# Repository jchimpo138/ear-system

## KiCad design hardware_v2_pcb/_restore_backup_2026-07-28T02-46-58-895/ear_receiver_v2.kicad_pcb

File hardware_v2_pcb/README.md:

# v2.0 Custom All-in-One Ear PCB Architecture (KiCad 10)

> **Overview:** Universal 25mm–30mm Circular All-in-One Custom PCB for Disney Interactive Ear Receiver Wearables.

---

## 1. Silicon Chipset Specifications

| Component Subsystem | Chipset / Part Number | Manufacturer | Key Specification / Function |
|---|---|---|---|
| **Microcontroller & BLE** | **nRF52840-QIAA** (or **nRF52840-MINI** module) | Nordic Semiconductor | 32-bit ARM Cortex-M4F, 4.8mA active BLE RX, 1.5µA System OFF sleep |
| **LiPo Battery Charger** | **MCP73831T-2ACI/OT** | Microchip | SOT-23-5 Linear Charger, $R_{\text{PROG}} = 2.0\text{k}\Omega$ (**Strict 500mA 1C MAX Limit**) |
| **5V LED Boost Converter** | **TPS61023DRLR** | Texas Instruments | Synchronous Step-Up Boost ($3.0\text{V}-4.2\text{V} \rightarrow 5.0\text{V} @ 3.0\text{A}$), 95% efficiency, `EN` pin control |
| **Battery Fuel Gauge** | **MAX17048G+T10** | Analog Devices / Maxim | I2C ModelGauge battery percentage % & voltage sensor |
| **Real-time Current Monitor** | **INA219AIDR** | Texas Instruments | I2C High-side current & power meter |
| **3-Axis Motion Sensor** | **LIS3DSH** (or **BMI270**) | STMicroelectronics / Bosch | I2C Accelerometer with `INT1` hardware wake interrupt pin |
| **Vibration Motor Driver** | **SI2302CDS-T1-GE3** | Vishay / Diodes Inc | N-Channel MOSFET ($V_{DS}=20\text{V}, I_D=2.8\text{A}$), SOT-23 package |
| **USB Charging Port** | **TYPE-C-31-M-12** (16-pin USB-C) | Midya / C&K | USB 2.0 16-pin USB-C connector with dual $5.1\text{k}\Omega$ CC pull-down resistors |

---

## 2. Pin Netlist Mapping (nRF52840)

| nRF52840 GPIO Pin | Connected Signal Net | Function |
|---|---|---|
| **P0.06** | `I2C_SDA` | Shared I2C Data Line (LIS3DSH, MAX17048, INA219) |
| **P0.08** | `I2C_SCL` | Shared I2C Clock Line (LIS3DSH, MAX17048, INA219) |
| **P0.10** | `MOTION_INT1` | Hardware Wake-On-Motion Interrupt from LIS3DSH |
| **P0.12** | `NEOPIXEL_DATA` | FastLED / WS2812B 2020 Data Signal Output |
| **P0.15** | `HAPTIC_PWM` | PWM Control Signal to SI2302 MOSFET Gate |
| **P0.17** | `BOOST_ENABLE` | High = Enable 5V Boost Converter, Low = Shut Down 5V Boost |
| **P0.20** | `KEY_BUTTON` | Input with Pull-Up for External Tactile Power Switch |

---

## 3. PCB Layout Guidelines
- **Board Shape:** Circular PCB, $\varnothing 25.0\text{mm} - 30.0\text{mm}$.
- **USB-C Placement:** Edge-mounted on the bottom perimeter.
- **Layer Count:** 2-Layer (or 4-Layer with internal GND / Power planes for optimal RF performance).
- **Antenna:** On-board Meander Inverted-F PCB Trace Antenna or 2.4GHz Chip Antenna.

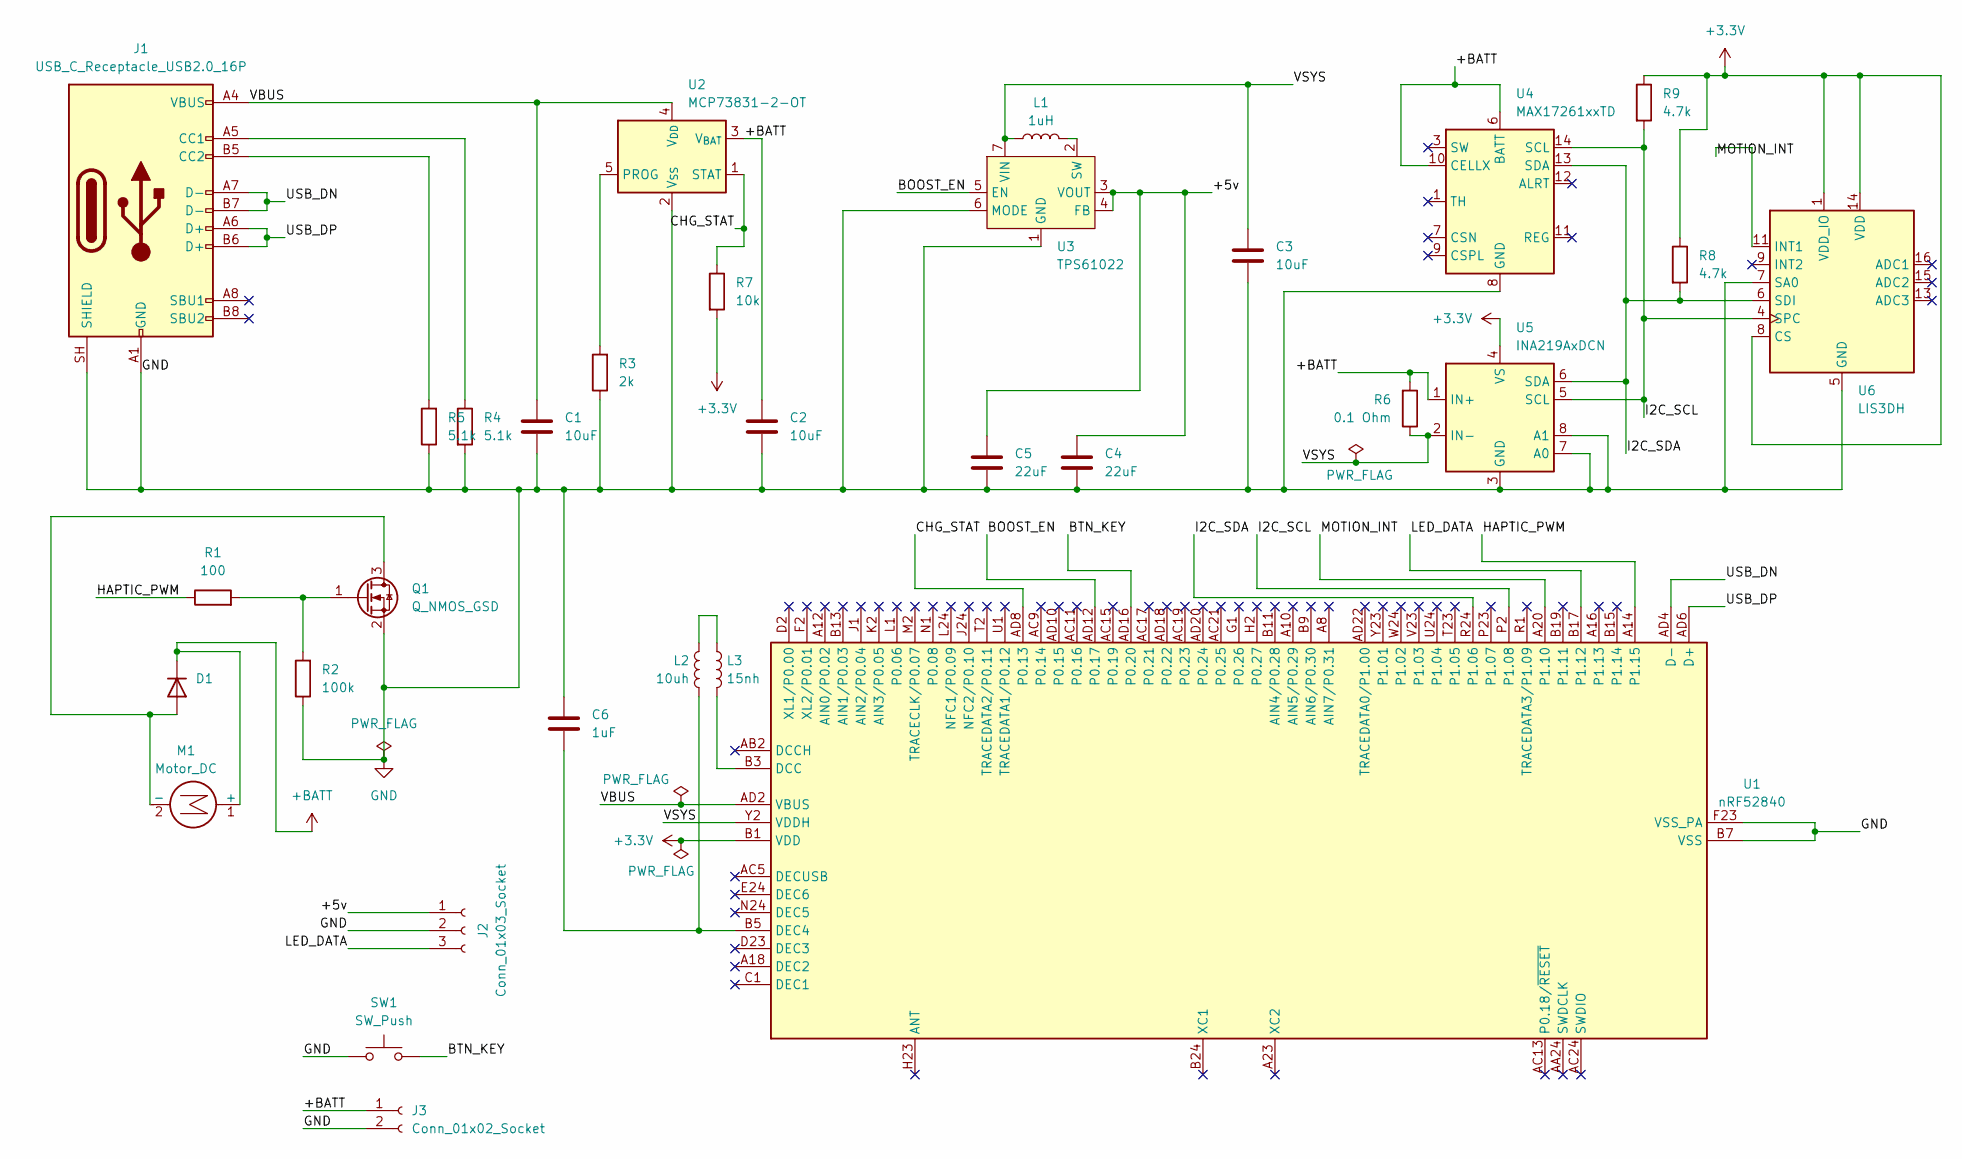
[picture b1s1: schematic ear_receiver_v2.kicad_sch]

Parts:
C1, C2, C3: 10uF; C_0603_1608Metric
C4, C5: 22uF; C_0603_1608Metric
C6: 1uF; C_0603_1608Metric
D1: 1N4148W; D_SOD-123
J1: USB_C_Receptacle_USB2.0_16P; USB_C_Receptacle_GCT_USB4105-xx-A_16P_TopMnt_Horizontal
J2: Conn_01x03_Socket; JST_PH_S3B-PH-K_1x03_P2.00mm_Horizontal
J3: Conn_01x02_Socket; JST_PH_S2B-PH-K_1x02_P2.00mm_Horizontal
L1: 1uH; L_0603_1608Metric
L2: 10uh; L_0402_1005Metric
L3: 15nh; L_0402_1005Metric
M1: Motor_DC; PinHeader_1x02_P2.54mm_Vertical
Q1: Q_NMOS_GSD; SOT-23
R1: 100; R_0603_1608Metric
R2: 100k; R_0603_1608Metric
R3: 2k; R_0603_1608Metric
R4, R5: 5.1k; R_0603_1608Metric
R6: 0.1 Ohm; R_1206_3216Metric
R7: 10k; R_0603_1608Metric
R8, R9: 4.7k; R_0603_1608Metric
SW1: SW_Push; SW_SPST_B3U-3000P-B
U1: nRF52840; Nordic_AQFN-73-1EP_7x7mm_P0.5mm
U2: MCP73831-2-OT; SOT-23-5
U3: TPS61022; Texas_RWU0007A_VQFN-7_2x2mm_P0.5mm
U4: MAX17261xxTD; TDFN-14-1EP_3x3mm_P0.4mm_EP1.78x2.35mm
U5: INA219AxDCN; SOT-23-8
U6: LIS3DH; LGA-16_3x3mm_P0.5mm_LayoutBorder3x5y

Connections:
+3.3V: R7.2, R8.1, R9.1, U1.A22 (VDD), U1.AD14 (VDD), U1.AD23 (VDD), U1.B1 (VDD), U1.W1 (VDD), U5.4 (VS), U6.1 (VDD_IO), U6.8 (CS), U6.14 (VDD)
+BATT: C2.2, D1.1 (K), J3.1, M1.1 (+), R6.2, U2.3 (V_{BAT}), U4.6 (BATT), U4.10 (CELLX), U5.1 (IN+)
/+5v: C4.1, C5.1, J2.1, U3.3 (VOUT), U3.4 (FB)
/BOOST_EN: U1.AD12 (P0.17), U3.5 (EN)
/BTN_KEY: SW1.2, U1.AD16 (P0.20)
/CHG_STAT: R7.1, U1.AD8 (P0.13), U2.1 (STAT)
/HAPTIC_PWM: R1.1, U1.A14 (P1.15)
/I2C_SCL: R9.2, U1.P2 (P1.08), U4.14 (SCL), U5.5 (SCL), U6.4 (SPC)
/I2C_SDA: R8.2, U1.R24 (P1.06), U4.13 (SDA), U5.6 (SDA), U6.6 (SDI)
/LED_DATA: J2.3, U1.B17 (P1.12)
/MOTION_INT: U1.A20 (P1.10), U6.11 (INT1)
/USB_DN: J1.A7 (D-), J1.B7 (D-), U1.AD4 (D-)
/USB_DP: J1.A6 (D+), J1.B6 (D+), U1.AD6 (D+)
/VBUS: C1.2, J1.A4 (VBUS), J1.A9 (VBUS), J1.B4 (VBUS), J1.B9 (VBUS), U1.AD2 (VBUS), U2.4 (V_{DD})
/VSYS: C3.1, L1.1, R6.1, U1.Y2 (VDDH), U3.7 (VIN), U5.2 (IN-)
GND: C1.1, C2.1, C3.2, C4.2, C5.2, C6.1, J1.A1 (GND), J1.A12 (GND), J1.B1 (GND), J1.B12 (GND), J1.SH (SHIELD), J2.2, J3.2, Q1.2 (S), R2.1, R3.1, R4.2, R5.1, SW1.1, U1.B7 (VSS), U1.EP (VSS), U1.F23 (VSS_PA), U2.2 (V_{SS}), U3.1 (GND), U3.6 (MODE), U4.8 (GND), U4.15 (GND), U5.3 (GND), U5.7 (A0), U5.8 (A1), U6.5 (GND), U6.7 (SA0), U6.10 (GND), U6.12 (GND)
unnamed: D1.2 (A), M1.2 (-), Q1.3 (D)
unnamed: J1.A5 (CC1), R4.1
unnamed: J1.B5 (CC2), R5.2
unnamed: L2.1, L3.1
unnamed: Q1.1 (G), R1.2, R2.2
unnamed: L3.2, U1.B3 (DCC)
unnamed: C6.2, L2.2, U1.B5 (DEC4)
unnamed: R3.2, U2.5 (PROG)
unnamed: L1.2, U3.2 (SW)

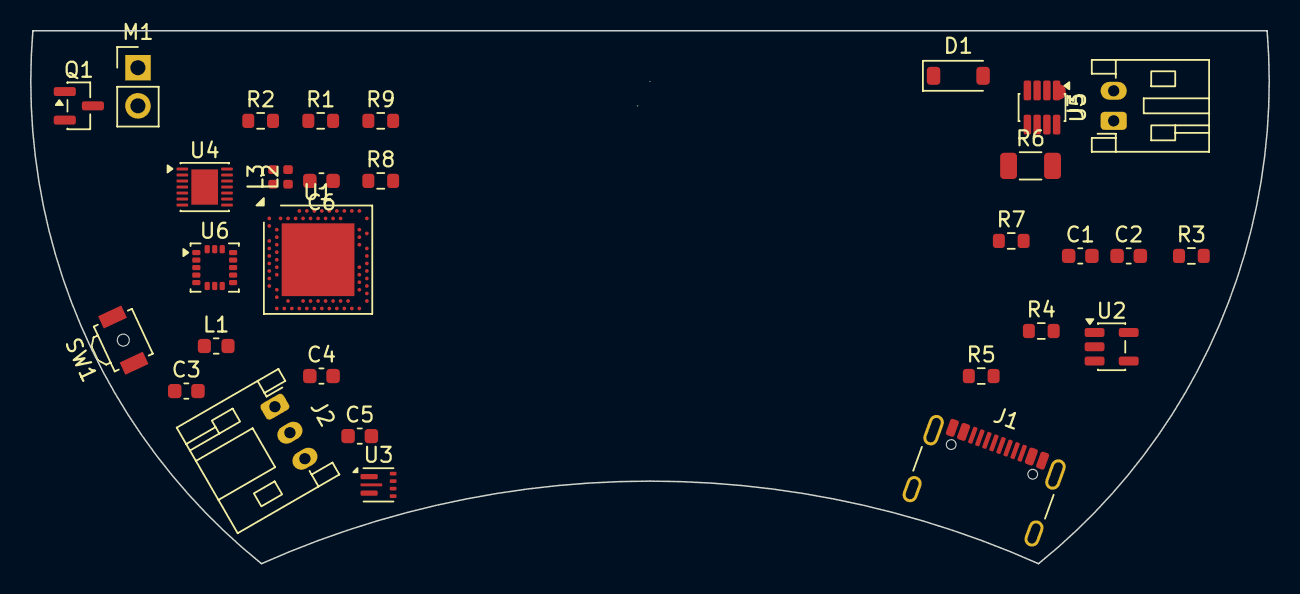
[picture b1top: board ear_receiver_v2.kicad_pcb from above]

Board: 2 copper layers, 82.5 x 35.5 mm, 31 parts (0 on the bottom side), 25 nets.
